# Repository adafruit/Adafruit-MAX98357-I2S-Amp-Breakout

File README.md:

## Adafruit MAX98357 I2S Amp Breakout PCB
<a href="http://www.adafruit.com/products/3006"><br/>
Click here to purchase one from the Adafruit shop</a>
<a href="http://www.adafruit.com/products/6513"><br/>
Click here to purchase one from the Adafruit shop</a>

The all in one digital audio amp breakout board that works incredibly well with the Raspberry Pi! If you're looking for an easy and low cost way to get you digital sound files bumpin' then the MAX98357 I2S Amp Breakout is for you. It takes standard I2S digital audio input and, not only decodes it into analog, but also amplifies it directly into a speaker. Perfect for adding compact amplified sound, it takes 2 breakouts (I2S DAC + Amp) and combines them into one.

I2S (not to be confused with I2C) in a digital sound protocol that is used on circuit boards to pass audio data around. Many high end chips and processors manage all of the audio in digital I2S format. Then, to input or output data, three or four pins are used (data in, data out, bit clock and left-right channel select). Usually, for audio devices, there's a DAC chip that will take I2S in and convert it to analog that can drive a headphone.

This small amplifier is surprisingly powerful - able to deliver 3.2 Watts of power into a 4 ohm impedance speaker (5V power @ 10% THD). Inside the miniature chip is a class D controller, able to run from 2.7V-5.5VDC. Since the amp is a class D, it's incredibly efficient - making it perfect for portable and battery-powered projects. It has built in thermal and over-current protection but we could barely tell it got hot.

PCB files for the Adafruit MAX98357 I2S Amp Breakouts
- https://www.adafruit.com/product/3006
- https://www.adafruit.com/product/6513

### License

Adafruit invests time and resources providing this open source design, please support Adafruit and open-source hardware by purchasing products from [Adafruit](https://www.adafruit.com)!

All text above must be included in any redistribution

Designed by Limor Fried/Ladyada for Adafruit Industries.
Creative Commons Attribution/Share-Alike, all text above must be included in any redistribution. 
See license.txt for additional information.

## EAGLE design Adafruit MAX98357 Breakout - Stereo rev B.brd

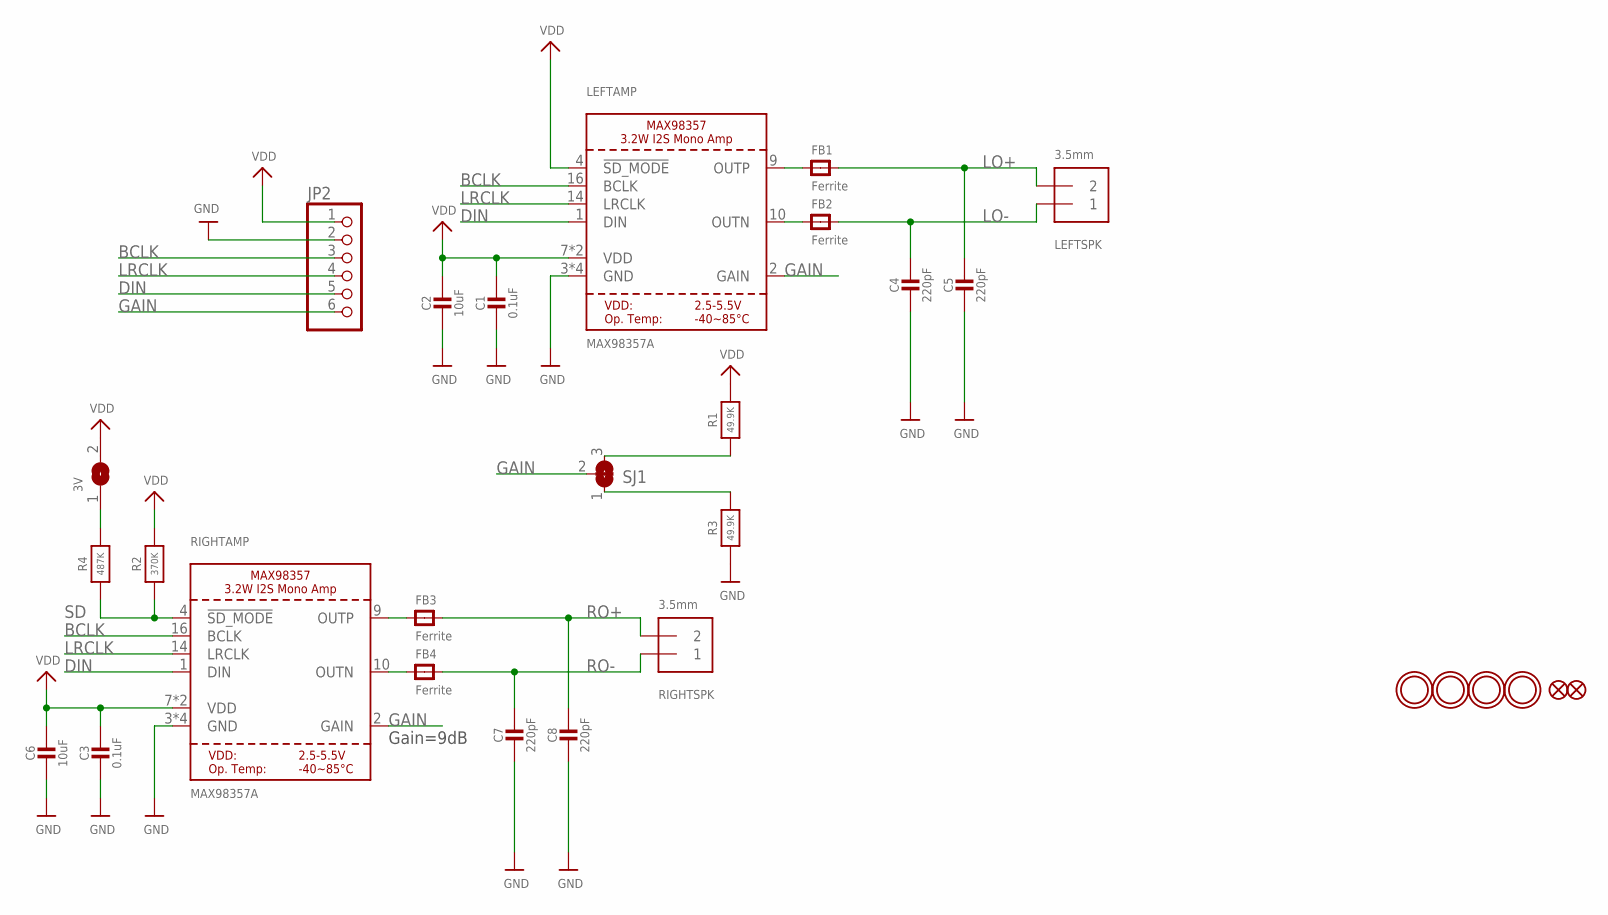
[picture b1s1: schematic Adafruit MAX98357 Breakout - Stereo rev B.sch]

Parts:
3V: SOLDERJUMPER; SOLDERJUMPER_ARROW_NOPASTE
C1, C3: 0.1uF; 0603-NO
C2, C6: 10uF; 0805-NO
C4, C5, C7, C8: 220pF; 0603-NO
FB1, FB2, FB3, FB4: Ferrite; 0603-NO
FID1, FID2: FIDUCIAL_0.5MM
JP2: HEADER-1X670MIL; 1X06_ROUND_70
LEFTAMP: MAX98357A; QFN16_3MM
LEFTSPK: 3.5mm; TERMBLOCK_1X2-3.5MM
R1, R3: 49.9K; 0603-NO
R2: 370K; 0603-NO
R4: 487K; 0603-NO
RIGHTAMP: MAX98357A; QFN16_3MM
RIGHTSPK: 3.5mm; TERMBLOCK_1X2-3.5MM
SJ1: SOLDERJUMPER_2WAY; SOLDERJUMPER_2WAY_OPEN_NOPASTE
U$9, U$10, U$23, U$24: MOUNTINGHOLE2.5; MOUNTINGHOLE_2.5_PLATED

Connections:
BCLK: JP2.3, LEFTAMP.16 (BCLK), RIGHTAMP.16 (BCLK)
DIN: JP2.5, LEFTAMP.1 (DIN), RIGHTAMP.1 (DIN)
GAIN: JP2.6, LEFTAMP.2 (GAIN), RIGHTAMP.2 (GAIN), SJ1.2
GND: C1.2, C2.2, C3.2, C4.2, C5.2, C6.2, C7.2, C8.2, JP2.2, LEFTAMP.3 (GND), LEFTAMP.11 (GND), LEFTAMP.15 (GND), LEFTAMP.THERMAL (GND), R3.1, RIGHTAMP.3 (GND), RIGHTAMP.11 (GND), RIGHTAMP.15 (GND), RIGHTAMP.THERMAL (GND)
LO+: C5.1, FB1.2, LEFTSPK.2
LO-: C4.1, FB2.2, LEFTSPK.1
LRCLK: JP2.4, LEFTAMP.14 (LRCLK), RIGHTAMP.14 (LRCLK)
unnamed: FB4.1, RIGHTAMP.10 (OUTN)
unnamed: FB3.1, RIGHTAMP.9 (OUTP)
unnamed: R3.2, SJ1.1
unnamed: 3V.1, R4.2
unnamed: FB2.1, LEFTAMP.10 (OUTN)
unnamed: FB1.1, LEFTAMP.9 (OUTP)
unnamed: R1.1, SJ1.3
RO+: C8.1, FB3.2, RIGHTSPK.2
RO-: C7.1, FB4.2, RIGHTSPK.1
SD: R2.1, R4.1, RIGHTAMP.4 (!SD_MODE)
VDD: 3V.2, C1.1, C2.1, C3.1, C6.1, JP2.1, LEFTAMP.4 (!SD_MODE), LEFTAMP.7 (VDD), LEFTAMP.8 (VDD), R1.2, R2.2, RIGHTAMP.7 (VDD), RIGHTAMP.8 (VDD)

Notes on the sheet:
Gain=9dB

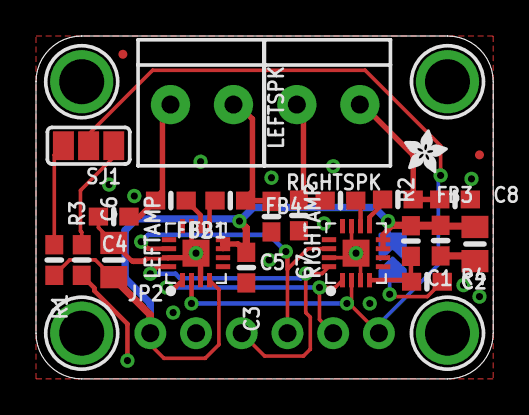
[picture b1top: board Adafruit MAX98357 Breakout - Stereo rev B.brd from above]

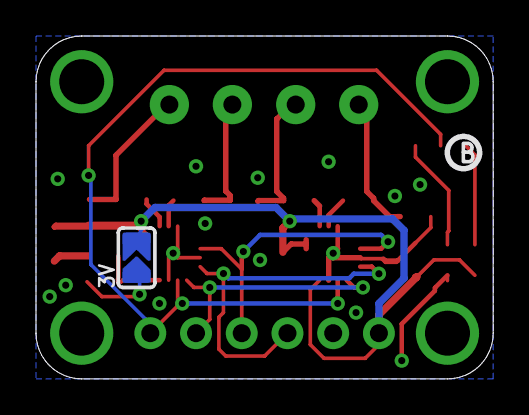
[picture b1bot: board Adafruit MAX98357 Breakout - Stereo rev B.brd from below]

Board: 2 copper layers, 25.4 x 19.1 mm, 51 parts (6 on the bottom side), 18 nets.

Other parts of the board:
PLABEL0: PLABEL0
PLABEL1: PLABEL1
PLABEL2: PLABEL2
PLABEL3: PLABEL3
PLABEL4: PLABEL4
PLABEL5: PLABEL5
PLABEL6: PLABEL6
PLABEL7: PLABEL7
PLABEL8: PLABEL8
PLABEL9: PLABEL9
PLABEL10: PLABEL10
PLABEL11: PLABEL11
PLABEL12: PLABEL12
PLABEL13: PLABEL13
PLABEL14: PLABEL14
PLABEL15: PLABEL15
PLABEL16: PLABEL16
PLABEL17: PLABEL17
PLABEL18: PLABEL18
PLABEL19: PLABEL19
U$14: ADAFRUIT_2.5MM
U$15: PCBFEAT-REV-040

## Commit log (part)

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2016-05-23 init

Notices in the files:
parts and their libraries:
microbuilder: This work is placed in the public domain, and may be freely used for commercial and non-commercial work with the following conditions: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
